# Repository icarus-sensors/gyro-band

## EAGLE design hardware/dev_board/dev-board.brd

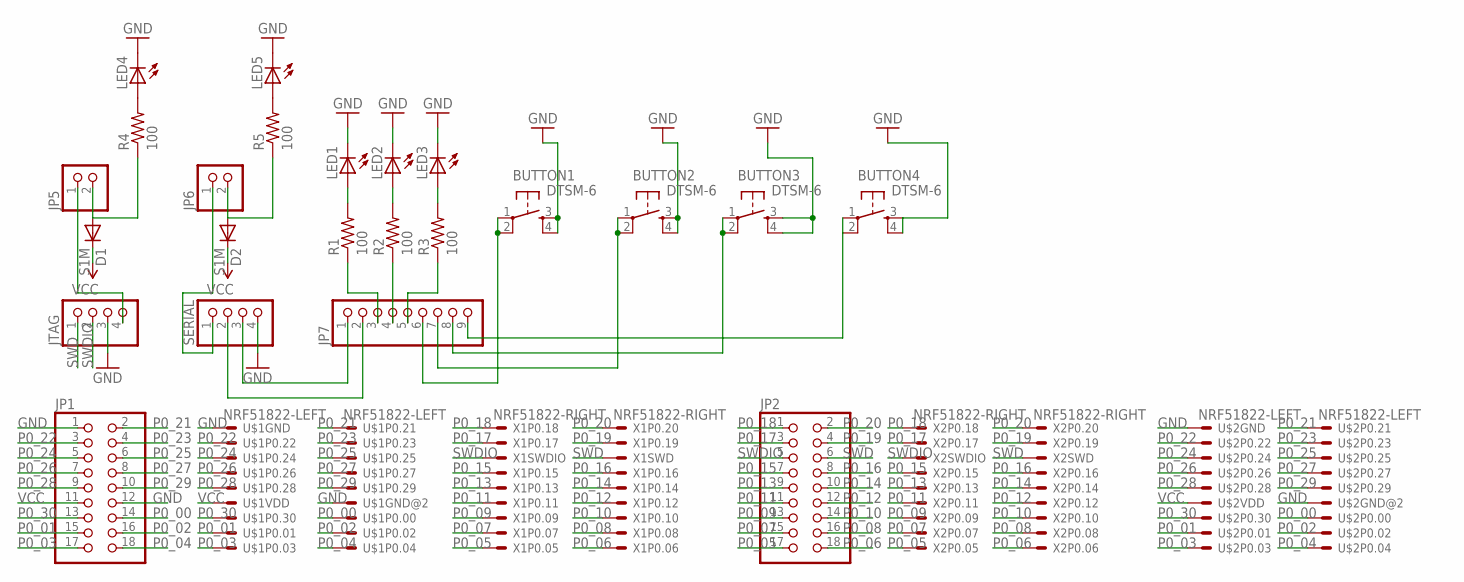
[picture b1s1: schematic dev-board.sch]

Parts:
BUTTON1, BUTTON2, BUTTON3, BUTTON4: DTSM-6
D1, D2: S1M; SMA
JP1, JP2: PINHD-2X9; 2X09
JP5, JP6: PINHD-1X2; 1X02
JP7: PINHD-1X9; 1X09
JTAG: PINHD-1X4; 1X04
LED1, LED2, LED3, LED4, LED5: LEDSML0603; SML0603
R1, R2, R3, R4, R5: 100; R0603
SERIAL: PINHD-1X4; 1X04
U$1, U$2: NRF51822-LEFT
X1, X2: NRF51822-RIGHT

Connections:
GND: BUTTON1.3, BUTTON1.4, BUTTON2.3, BUTTON2.4, BUTTON3.3, BUTTON3.4, BUTTON4.3, BUTTON4.4, JP1.1, JP1.12, JTAG.3, LED1.C, LED2.C, LED3.C, LED4.C, LED5.C, SERIAL.4, U$1.1, U$1.12, U$2.1, U$2.12
unnamed: LED1.A, R1.2
unnamed: LED2.A, R2.2
unnamed: LED3.A, R3.2
unnamed: JP7.1, SERIAL.3
unnamed: JP7.2, SERIAL.2
unnamed: JP6.1, SERIAL.1
unnamed: JP7.3, R1.1
unnamed: JP7.4, R2.1
unnamed: JP5.1, JTAG.4
unnamed: JP7.5, R3.1
unnamed: BUTTON3.1, BUTTON3.2, JP7.8
unnamed: LED4.A, R4.2
unnamed: BUTTON2.1, BUTTON2.2, JP7.7
unnamed: LED5.A, R5.2
unnamed: BUTTON1.1, BUTTON1.2, JP7.6
unnamed: BUTTON4.1, BUTTON4.2, JP7.9
unnamed: D1.A, JP5.2, R4.1
unnamed: D2.A, JP6.2, R5.1
P0_00: JP1.14, U$1.14, U$2.14
P0_01: JP1.15, U$1.15, U$2.15
P0_02: JP1.16, U$1.16, U$2.16
P0_03: JP1.17, U$1.17, U$2.17
P0_04: JP1.18, U$1.18, U$2.18
P0_05: JP2.17, X1.17, X2.17
P0_06: JP2.18, X1.18, X2.18
P0_07: JP2.15, X1.15, X2.15
P0_08: JP2.16, X1.16, X2.16
P0_09: JP2.13, X1.13, X2.13
P0_10: JP2.14, X1.14, X2.14
P0_11: JP2.11, X1.11, X2.11
P0_12: JP2.12, X1.12, X2.12
P0_13: JP2.9, X1.9, X2.9
P0_14: JP2.10, X1.10, X2.10
P0_15: JP2.7, X1.7, X2.7
P0_16: JP2.8, X1.8, X2.8
P0_17: JP2.3, X1.3, X2.3
P0_18: JP2.1, X1.1, X2.1
P0_19: JP2.4, X1.4, X2.4
P0_20: JP2.2, X1.2, X2.2
P0_21: JP1.2, U$1.2, U$2.2
P0_22: JP1.3, U$1.3, U$2.3
P0_23: JP1.4, U$1.4, U$2.4
P0_24: JP1.5, U$1.5, U$2.5
P0_25: JP1.6, U$1.6, U$2.6
P0_26: JP1.7, U$1.7, U$2.7
P0_27: JP1.8, U$1.8, U$2.8
P0_28: JP1.9, U$1.9, U$2.9
P0_29: JP1.10, U$1.10, U$2.10
P0_30: JP1.13, U$1.13, U$2.13
SWD: JP2.6, JTAG.1, X1.6, X2.6
SWDIO: JP2.5, JTAG.2, X1.5, X2.5
VCC: D1.C, D2.C, JP1.11, U$1.11, U$2.11

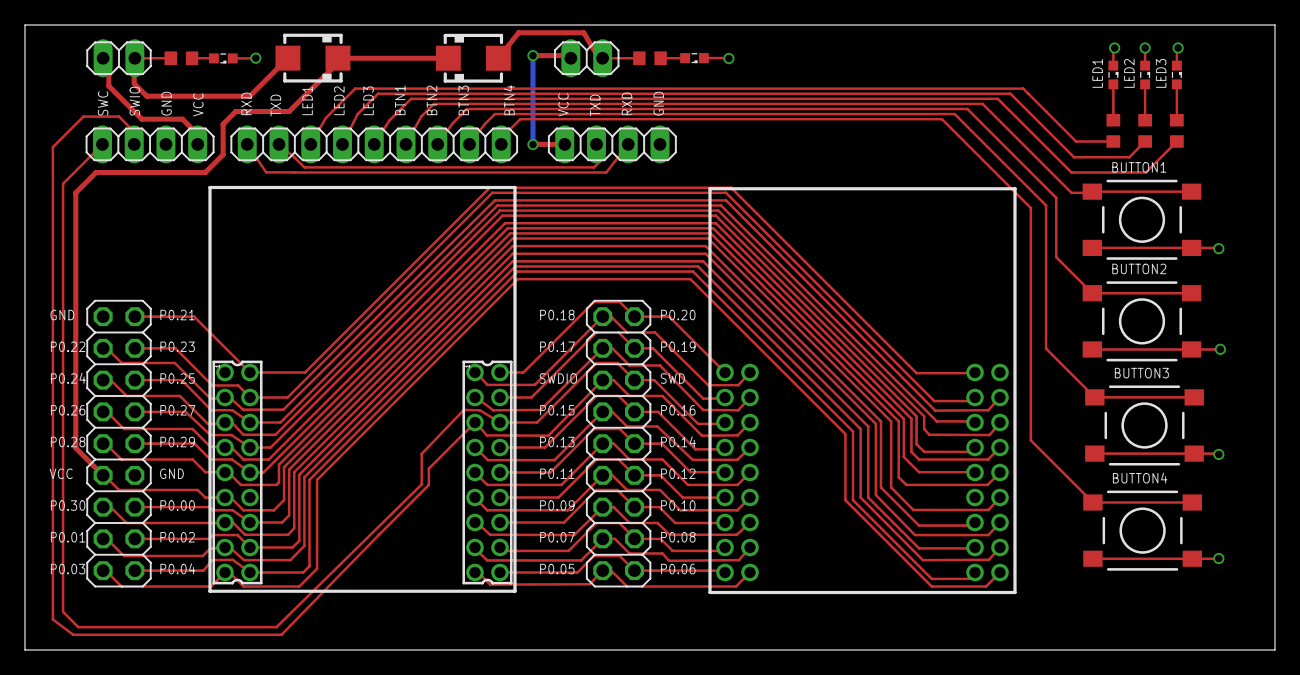
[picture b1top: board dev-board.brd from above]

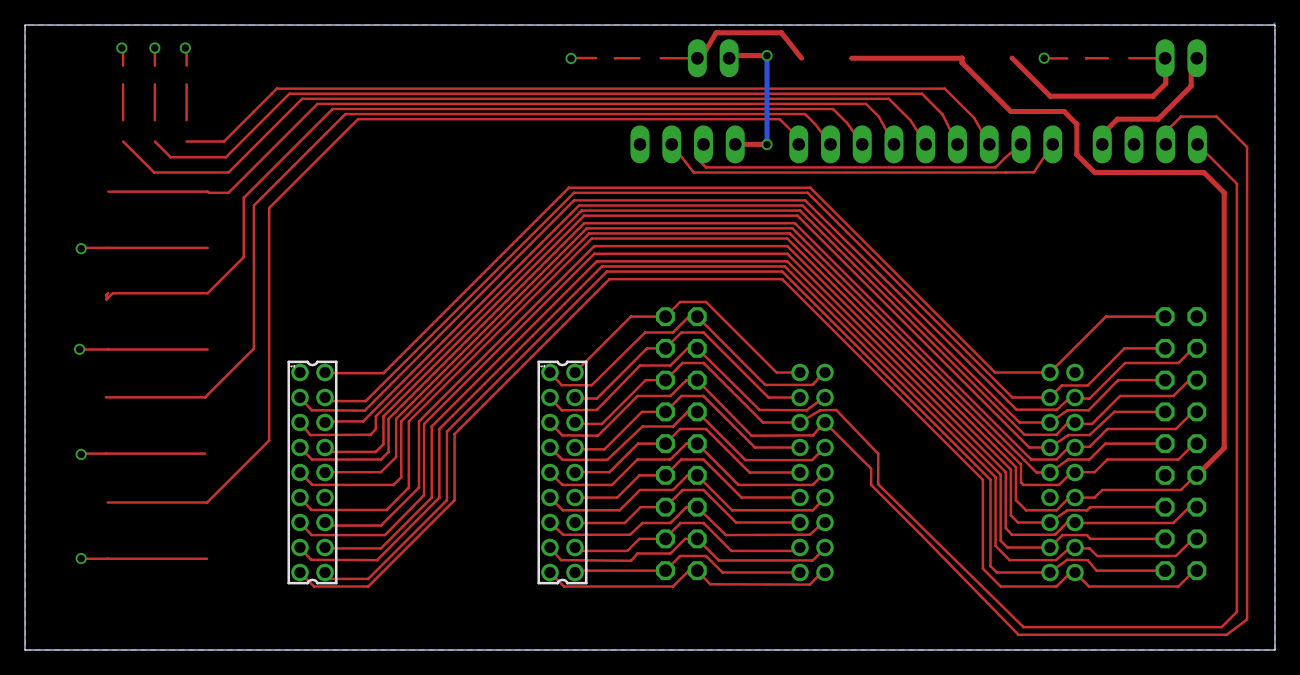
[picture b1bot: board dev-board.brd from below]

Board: 2 copper layers, 100.0 x 50.0 mm, 27 parts (2 on the bottom side), 53 nets.

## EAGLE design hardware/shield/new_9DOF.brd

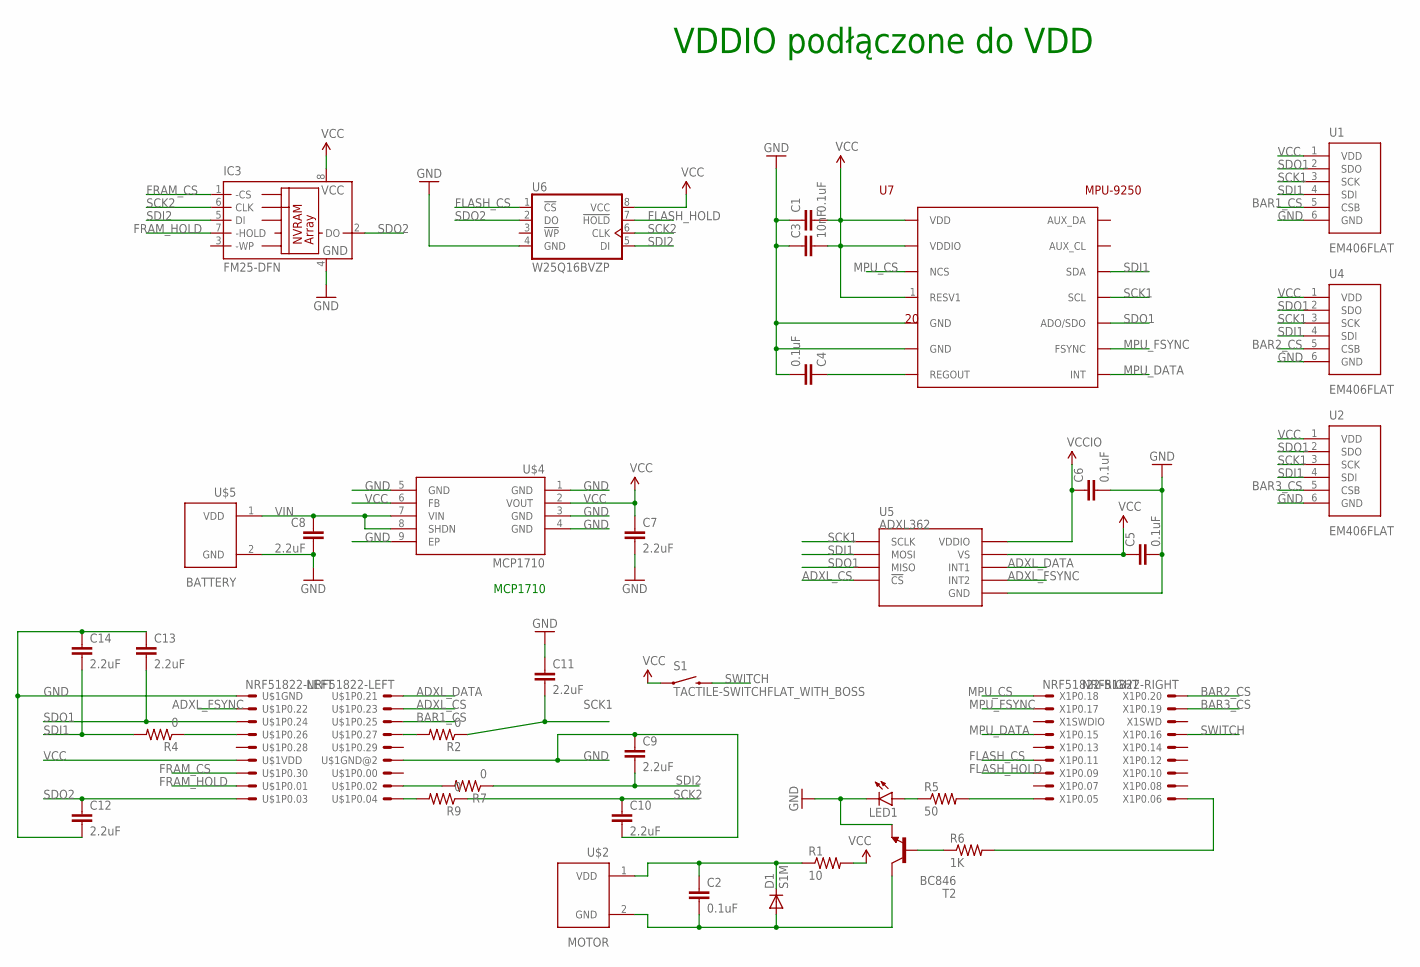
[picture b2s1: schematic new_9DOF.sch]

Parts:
C1, C2, C4, C5, C6: 0.1uF; 0603-CAP
C3: 10nF; 0603-CAP
C7, C8, C9, C10, C11, C12, C13, C14: 2.2uF; 0603-CAP
D1: S1M; SMA
IC3: FM25-DFN; DFN-8
LED1: LED0603; LED-0603
R1: 10; 0603-RES
R2, R4, R7, R9: 0; 0603-RES
R5: 50; 0603-RES
R6: 1K; 0603-RES
S1: TACTILE-SWITCHFLAT_WITH_BOSS; TACTILE-SWITCH-SMD
T2: BC846; SOT23
U1, U2, U4: EM406FLAT; EM406-FLAT
U5: ADXL362; ADXL362-1:1
U6: W25Q16BVZP; WSON8
U7: MPU-9250
U$1: NRF51822-LEFT
U$2: MOTOR; EM406-2PIN
U$4: MCP1710
U$5: BATTERY; EM406-2PIN
X1: NRF51822-RIGHT

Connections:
ADXL_CS: U5.P$8 (!CS), U$1.4
ADXL_DATA: U5.P$11 (INT1), U$1.2
ADXL_FSYNC: U5.P$9 (INT2), U$1.3
BAR1_CS: U1.5 (CSB), U$1.6
BAR2_CS: U4.5 (CSB), X1.2
BAR3_CS: U2.5 (CSB), X1.4
FLASH_CS: U6.1 (!CS!), X1.11
FLASH_HOLD: U6.7 (!HOLD!), X1.13
FRAM_CS: IC3.1 (-CS), U$1.13
FRAM_HOLD: IC3.7 (-HOLD), U$1.15
GND: C1.1, C3.1, C4.2, C5.2, C6.2, C7.2, C8.2, C9.1, C10.2, C11.1, C12.2, C13.1, C14.1, IC3.4 (GND), LED1.C, T2.2 (E), U1.6 (GND), U2.6 (GND), U4.6 (GND), U5.P$12 (GND), U5.P$13 (GND), U5.P$16 (GND), U6.4 (GND), U7.18 (GND), U7.20 (GND), U$1.1, U$1.12, U$4.1 (GND), U$4.3 (GND), U$4.4 (GND), U$4.5 (GND), U$4.9 (EP), U$5.2 (GND)
MPU_CS: U7.22 (NCS), X1.1
MPU_DATA: U7.12 (INT), X1.7
MPU_FSYNC: U7.11 (FSYNC), X1.3
unnamed: C4.1, U7.10 (REGOUT)
unnamed: C2.1, D1.C, R1.1, U$2.1 (VDD)
unnamed: R4.1, U$1.7
unnamed: R2.2, U$1.8
unnamed: R7.2, U$1.16
unnamed: R5.2, X1.17
unnamed: R9.2, U$1.18
unnamed: LED1.A, R5.1
unnamed: C2.2, D1.A, T2.3 (C), U$2.2 (GND)
unnamed: R6.2, X1.18
unnamed: R6.1, T2.1 (B)
SCK1: C11.2, R2.1, U1.3 (SCK), U2.3 (SCK), U4.3 (SCK), U5.P$4 (SCLK), U7.23 (SCL)
SCK2: C10.1, IC3.6 (CLK), R9.1, U6.6 (CLK)
SDI1: C14.2, R4.2, U1.4 (SDI), U2.4 (SDI), U4.4 (SDI), U5.P$6 (MOSI), U7.24 (SDA)
SDI2: C9.2, IC3.5 (DI), R7.1, U6.5 (DI)
SDO1: C13.2, U1.2 (SDO), U2.2 (SDO), U4.2 (SDO), U5.P$7 (MISO), U7.9 (ADO/SDO), U$1.5
SDO2: C12.1, IC3.2 (DO), U6.2 (DO), U$1.17
SWITCH: S1.2, X1.8
VCC: C1.2, C3.2, C5.1, C7.1, IC3.8 (VCC), R1.2, S1.1, U1.1 (VDD), U2.1 (VDD), U4.1 (VDD), U5.P$14 (VS), U6.8 (VCC), U7.1 (RESV1), U7.8 (VDDIO), U7.13 (VDD), U$1.11, U$4.2 (VOUT), U$4.6 (FB)
VCCIO: C6.1, U5.P$1 (VDDIO)
VIN: C8.1, U$4.7 (VIN), U$4.8 (SHDN), U$5.1 (VDD)

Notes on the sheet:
MCP1710
VDDIO podłączone do VDD

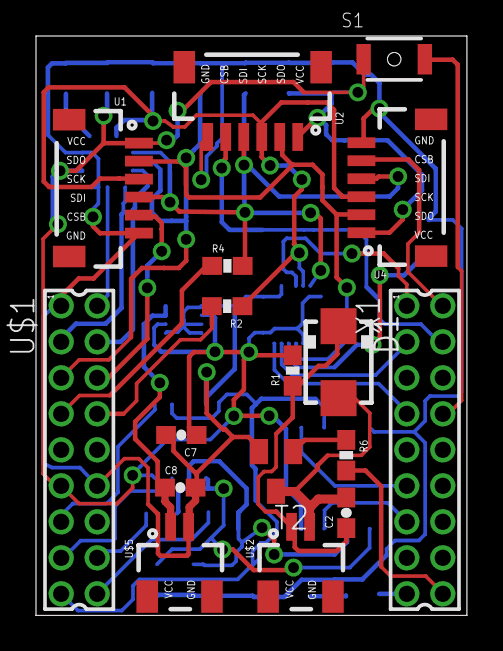
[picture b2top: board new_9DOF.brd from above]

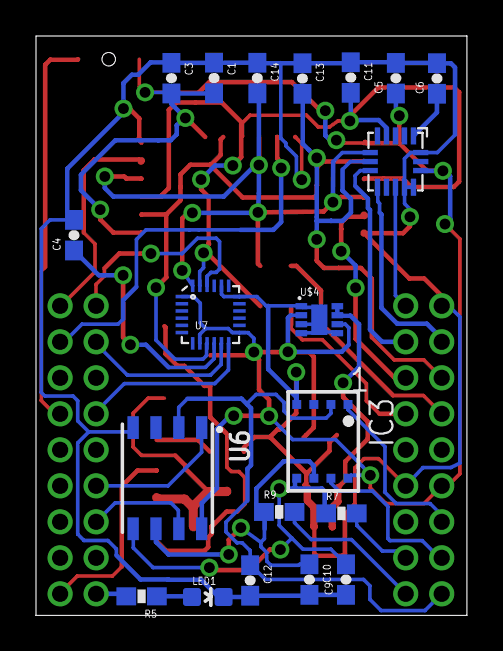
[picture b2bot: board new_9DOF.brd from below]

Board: 2 copper layers, 23.9 x 32.2 mm, 37 parts (20 on the bottom side), 35 nets.

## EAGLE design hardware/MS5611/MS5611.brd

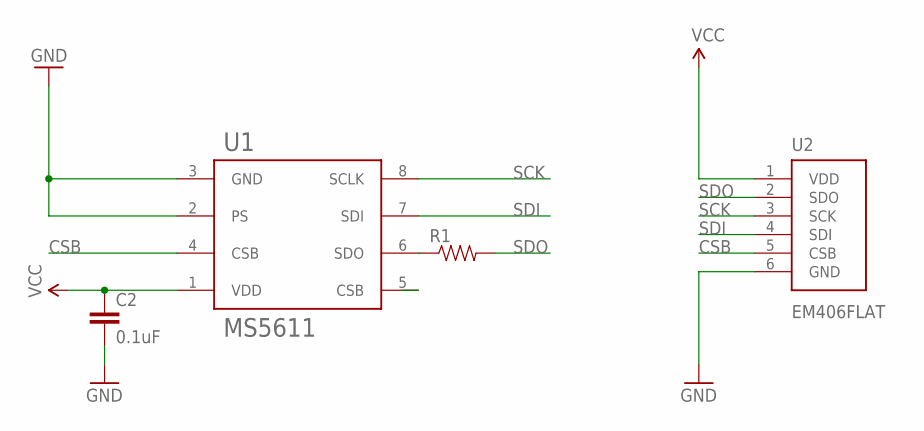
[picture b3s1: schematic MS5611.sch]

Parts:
C2: 0.1uF; 0603-CAP
R1: RESISTOR0603-RES; 0603-RES
U1: MS5611; QFN-8
U2: EM406FLAT; EM406-FLAT

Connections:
CSB: U1.4 (CSB), U2.5 (CSB)
GND: C2.2, U1.2 (PS), U1.3 (GND), U2.6 (GND)
unnamed: R1.1, U1.6 (SDO)
SCK: U1.8 (SCLK), U2.3 (SCK)
SDI: U1.7 (SDI), U2.4 (SDI)
SDO: R1.2, U2.2 (SDO)
VCC: C2.1, U1.1 (VDD), U2.1 (VDD)

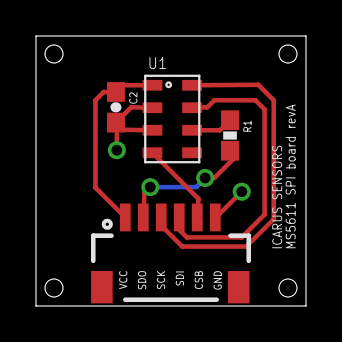
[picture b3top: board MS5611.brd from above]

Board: 2 copper layers, 15.0 x 15.0 mm, 4 parts (0 on the bottom side), 7 nets.

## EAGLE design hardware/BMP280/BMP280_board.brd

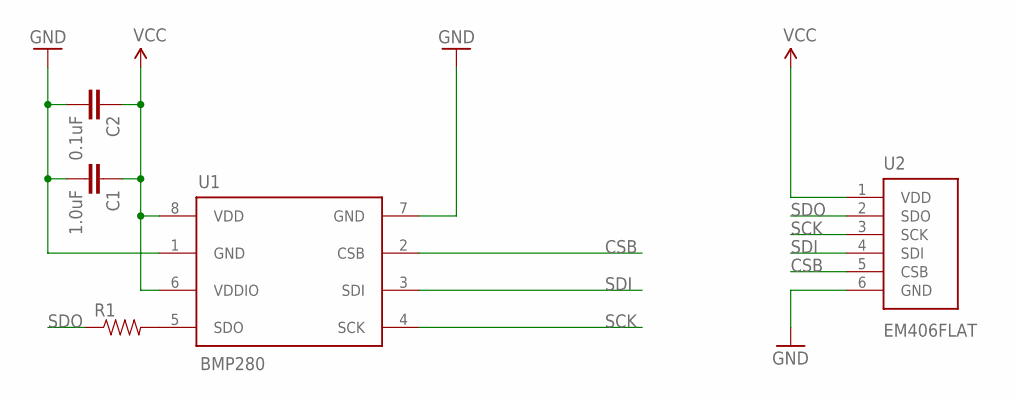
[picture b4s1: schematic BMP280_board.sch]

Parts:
C1: 1.0uF; 0603-CAP
C2: 0.1uF; 0603-CAP
R1: RESISTOR0603-RES; 0603-RES
U1: BMP280; LGA-8
U2: EM406FLAT; EM406-FLAT

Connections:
CSB: U1.2 (CSB), U2.5 (CSB)
GND: C1.2, C2.2, U1.1 (GND), U1.7 (GND), U2.6 (GND)
unnamed: R1.2, U1.5 (SDO)
SCK: U1.4 (SCK), U2.3 (SCK)
SDI: U1.3 (SDI), U2.4 (SDI)
SDO: R1.1, U2.2 (SDO)
VCC: C1.1, C2.1, U1.6 (VDDIO), U1.8 (VDD), U2.1 (VDD)

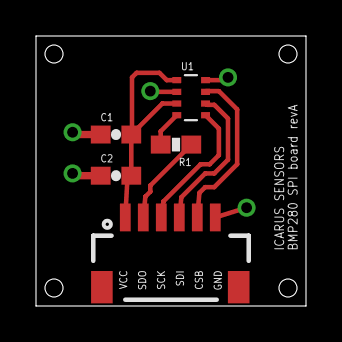
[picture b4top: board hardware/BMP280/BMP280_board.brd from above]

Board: 2 copper layers, 15.0 x 15.0 mm, 5 parts (0 on the bottom side), 7 nets.

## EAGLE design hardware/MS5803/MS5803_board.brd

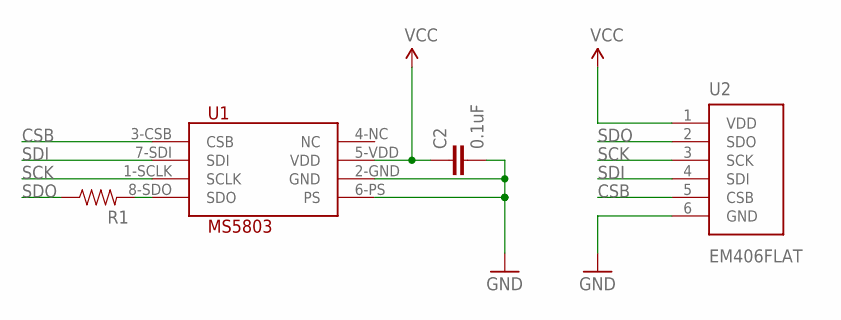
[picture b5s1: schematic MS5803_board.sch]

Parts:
C2: 0.1uF; 0603-CAP
R1: 0; 0603-RES
U1: MS5803
U2: EM406FLAT; EM406-FLAT

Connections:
CSB: U1.3-CSB (CSB), U2.5 (CSB)
GND: C2.2, U1.2-GND (GND), U1.6-PS (PS), U2.6 (GND)
unnamed: R1.2, U1.8-SDO (SDO)
SCK: U1.1-SCLK (SCLK), U2.3 (SCK)
SDI: U1.7-SDI (SDI), U2.4 (SDI)
SDO: R1.1, U2.2 (SDO)
VCC: C2.1, U1.5-VDD (VDD), U2.1 (VDD)

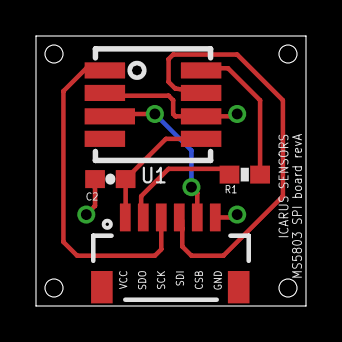
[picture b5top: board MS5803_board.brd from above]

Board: 2 copper layers, 15.0 x 15.0 mm, 4 parts (0 on the bottom side), 7 nets.

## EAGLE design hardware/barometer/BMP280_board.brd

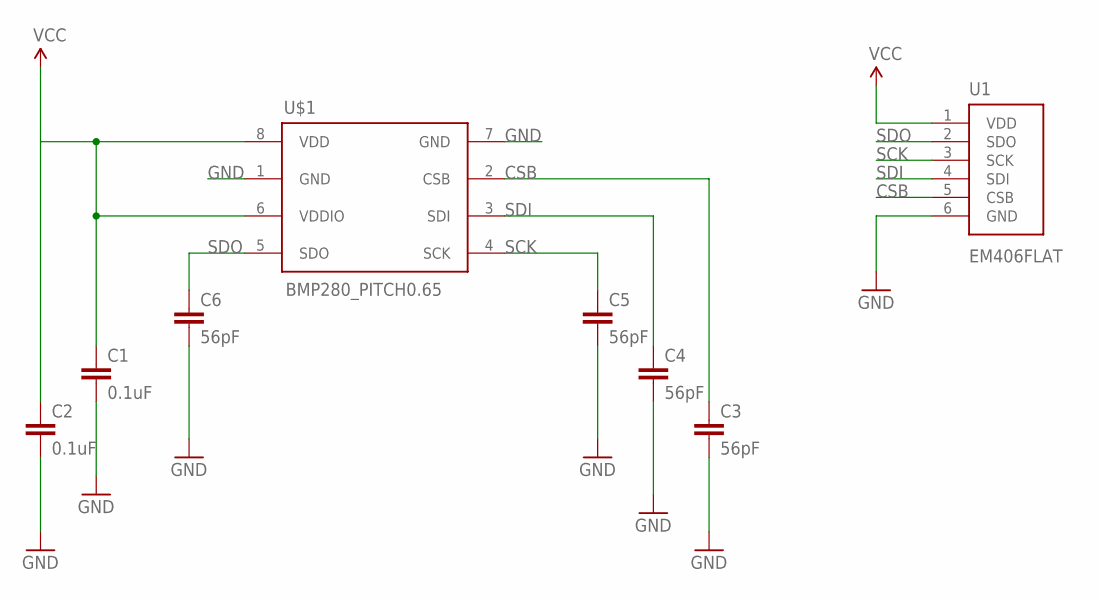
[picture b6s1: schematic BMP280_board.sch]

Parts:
C1, C2: 0.1uF; 0603-CAP
C3, C4, C5, C6: 56pF; 0603-CAP
U1: EM406FLAT; EM406-FLAT
U$1: BMP280_PITCH0.65; LGA-8

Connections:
CSB: C3.1, U1.5 (CSB), U$1.2 (CSB)
GND: C1.2, C2.2, C3.2, C4.2, C5.2, C6.2, U1.6 (GND), U$1.1 (GND), U$1.7 (GND)
SCK: C5.1, U1.3 (SCK), U$1.4 (SCK)
SDI: C4.1, U1.4 (SDI), U$1.3 (SDI)
SDO: C6.1, U1.2 (SDO), U$1.5 (SDO)
VCC: C1.1, C2.1, U1.1 (VDD), U$1.6 (VDDIO), U$1.8 (VDD)

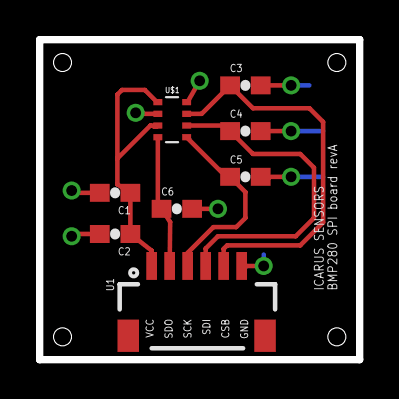
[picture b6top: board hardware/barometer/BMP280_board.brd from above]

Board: 2 copper layers, 17.8 x 17.8 mm, 8 parts (0 on the bottom side), 6 nets.

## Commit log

2014-11-28 first revision of barometer board
2014-12-06 schematic layout
2014-12-06 barometeres
2014-12-06 remove .DS_Store
2014-12-06 BMP280
2014-12-06 MS5611
2014-12-06 MS5803
2014-12-06 borderless
2014-12-08 initial shield
2014-12-10 shield
2015-04-28 add 9DOF schematics
2015-05-05 production board
2015-05-24 3D cases
2015-05-24 slight revisions
2015-05-25 3D print profile for Repetier
2015-06-17 added dev board

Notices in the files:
parts and their libraries:
SparkFun-Capacitors: Licensing: Creative Commons ShareAlike 4.0 International - https://creativecommons.org/licenses/by-sa/4.0
